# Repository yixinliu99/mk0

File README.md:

# mk0
Modularized Keyboard 0

The goal of this project is to build a full-fledged and modularized keyboard from scratch, including PCBs and a case.

# Prelude
The last time I designed a PCB was for the final project of my Bachelor degree, which was almost 4 years ago. Some refreshing on how to design PCB is definetely needed for me. I have found https://wiki.ai03.com/books/pcb-design/chapter/pcb-designer-guide pretty useful as it covers not only general PCB designing but also how keyboards work.

# Roadmap
- PCB design (keyboard + STM32F303)
- Firmware. Probably will use some code from QMK (https://github.com/qmk/qmk_firmware)
- Case design
- Fabrication

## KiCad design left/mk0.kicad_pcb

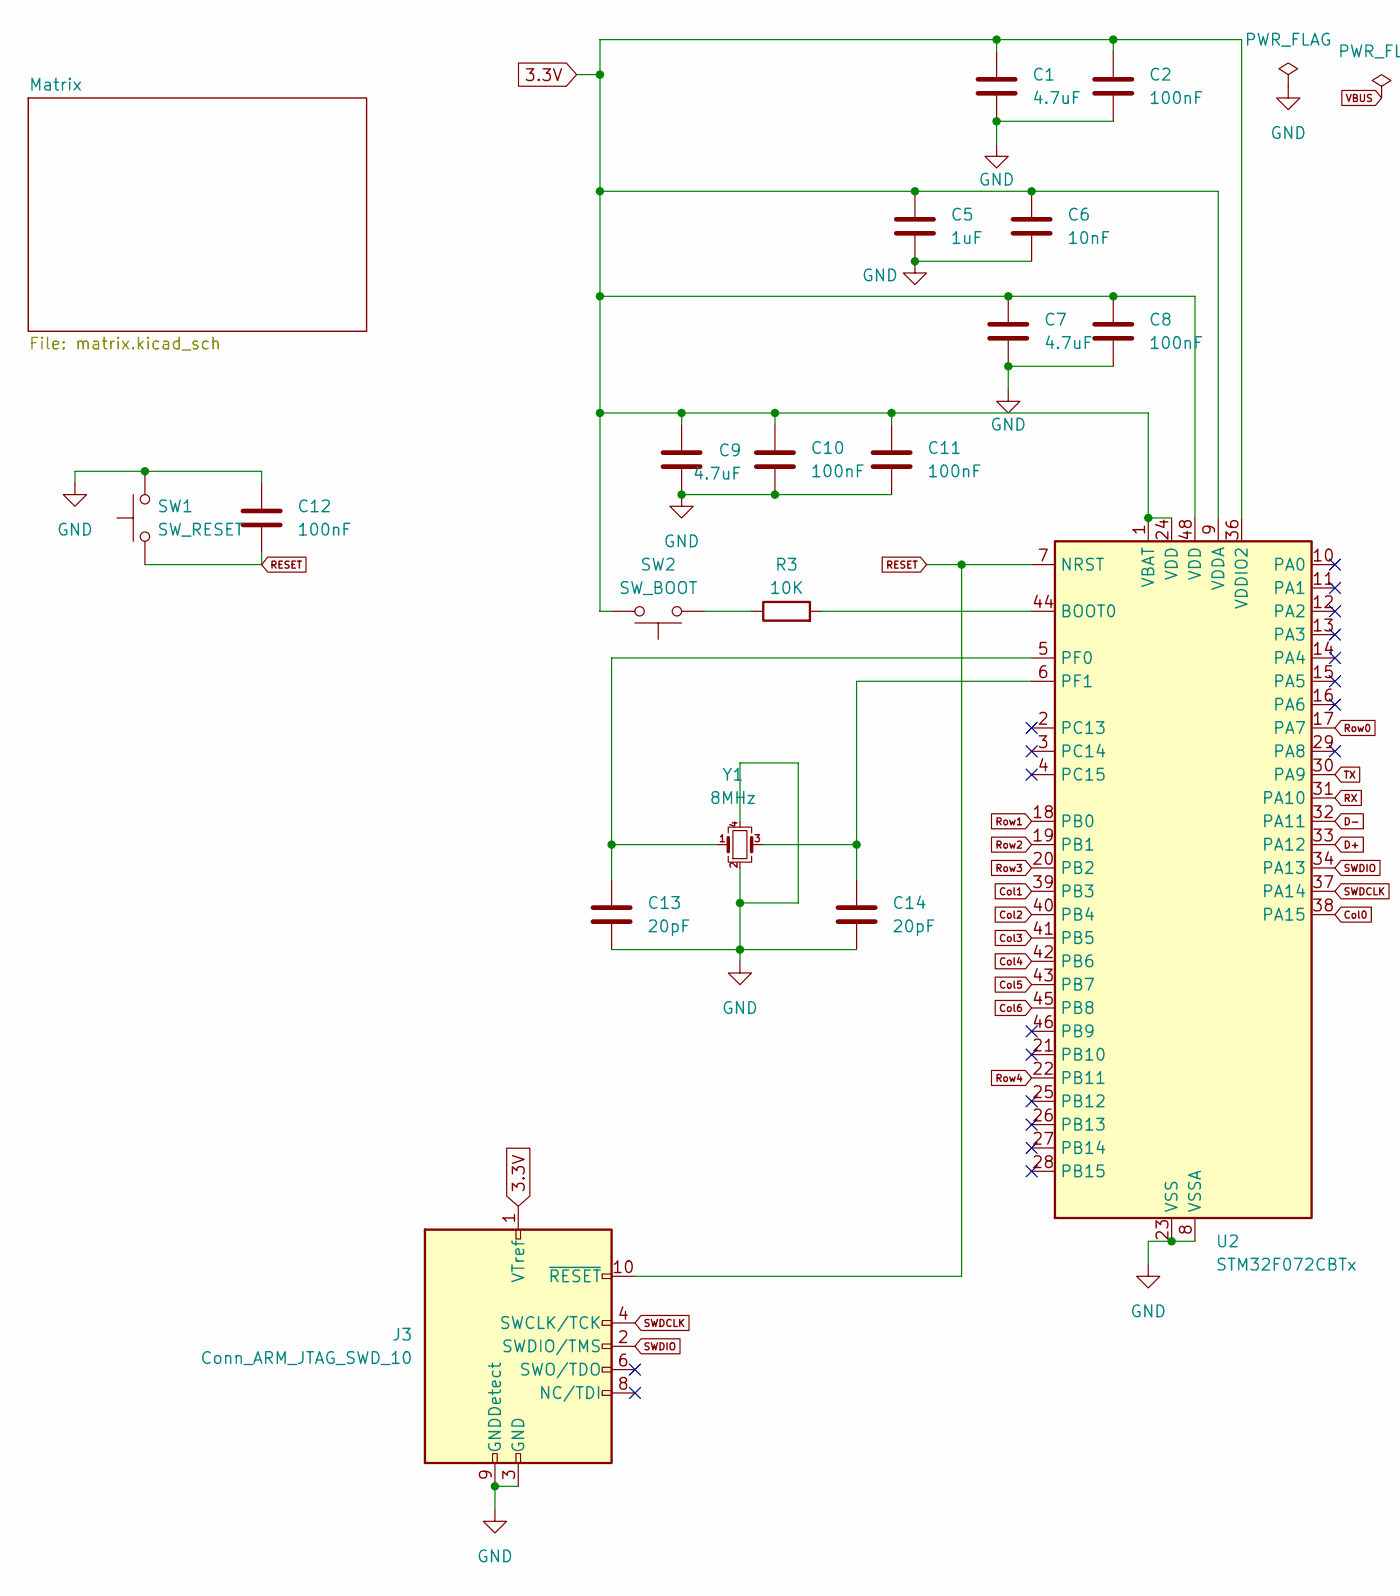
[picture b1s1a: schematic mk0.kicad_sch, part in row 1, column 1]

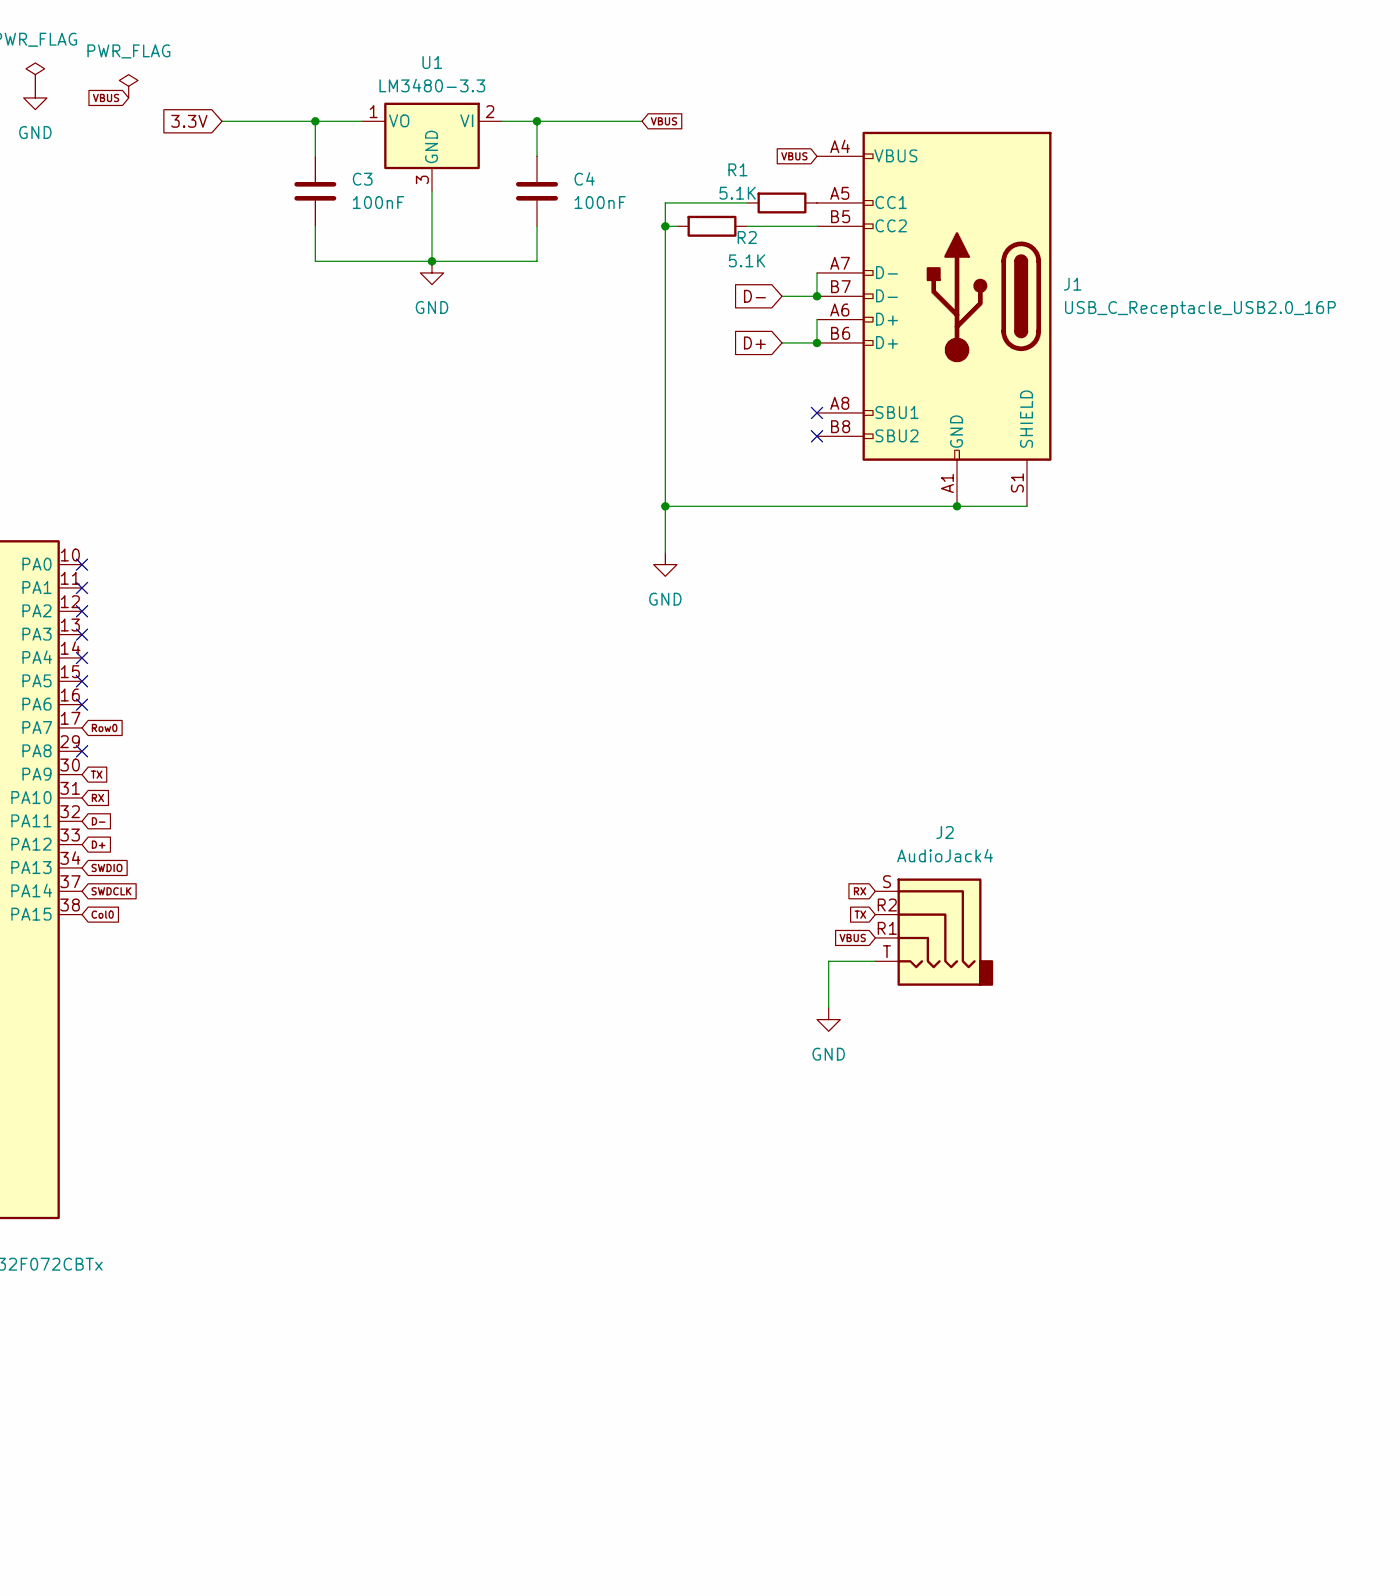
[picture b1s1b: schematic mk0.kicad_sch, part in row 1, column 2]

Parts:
C1, C7, C9: 4.7uF; C_0805_2012Metric_Pad1.18x1.45mm_HandSolder
C2, C3, C4, C8, C10, C11, C12: 100nF; C_0805_2012Metric_Pad1.18x1.45mm_HandSolder
C5: 1uF; C_0805_2012Metric_Pad1.18x1.45mm_HandSolder
C6: 10nF; C_0805_2012Metric_Pad1.18x1.45mm_HandSolder
C13, C14: 20pF; C_0805_2012Metric_Pad1.18x1.45mm_HandSolder
J1: USB_C_Receptacle_USB2.0_16P; USB_C_Receptacle_HRO_TYPE-C-31-M-12
J2: AudioJack4; Plug_3.5mm_CUI_SP-3541
J3: Conn_ARM_JTAG_SWD_10; Harwin_M20-89010xx_1x10_P2.54mm_Horizontal
R1, R2: 5.1K; R_0805_2012Metric_Pad1.20x1.40mm_HandSolder
R3: 10K; R_0805_2012Metric_Pad1.20x1.40mm_HandSolder
SW1: SW_RESET; SW_SPST_CK_RS282G05A3
SW2: SW_BOOT; SW_SPST_CK_RS282G05A3
U1: LM3480-3.3; SOT-23
U2: STM32F072CBTx; LQFP-48_7x7mm_P0.5mm
Y1: 8MHz; Crystal_SMD_3225-4Pin_3.2x2.5mm_HandSoldering

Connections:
3.3V: C1.1, C2.1, C3.1, C5.1, C6.1, C7.1, C8.1, C9.1, C10.1, C11.1, J3.1 (VTref), SW2.2, U1.1 (VO), U2.1 (VBAT), U2.9 (VDDA), U2.24 (VDD), U2.36 (VDDIO2), U2.48 (VDD)
Col0: U2.38 (PA15); also elsewhere on the board
Col1: U2.39 (PB3); also elsewhere on the board
Col2: U2.40 (PB4); also elsewhere on the board
Col3: U2.41 (PB5); also elsewhere on the board
Col4: U2.42 (PB6); also elsewhere on the board
Col5: U2.43 (PB7); also elsewhere on the board
Col6: U2.45 (PB8); also elsewhere on the board
D+: J1.A6 (D+), J1.B6 (D+), U2.33 (PA12)
D-: J1.A7 (D-), J1.B7 (D-), U2.32 (PA11)
GND: C1.2, C2.2, C3.2, C4.2, C5.2, C6.2, C7.2, C8.2, C9.2, C10.2, C11.2, C12.1, C13.2, C14.2, J1.A1 (GND), J1.A12 (GND), J1.B1 (GND), J1.B12 (GND), J1.S1 (SHIELD), J2.T, J3.3 (GND), J3.5 (GND), J3.9 (GNDDetect), R1.2, R2.2, SW1.2, U1.3 (GND), U2.8 (VSSA), U2.23 (VSS), U2.35 (VSS), U2.47 (VSS), Y1.2, Y1.4
unnamed: J1.A5 (CC1), R1.1
unnamed: J1.B5 (CC2), R2.1
unnamed: R3.1, SW2.1
unnamed: R3.2, U2.44 (BOOT0)
unnamed: C13.1, U2.5 (PF0), Y1.1
unnamed: C14.1, U2.6 (PF1), Y1.3
RESET: C12.2, J3.10 (~RESET), SW1.1, U2.7 (NRST)
RX: J2.S, U2.31 (PA10)
Row0: U2.17 (PA7); also elsewhere on the board
Row1: U2.18 (PB0); also elsewhere on the board
Row2: U2.19 (PB1); also elsewhere on the board
Row3: U2.20 (PB2); also elsewhere on the board
Row4: U2.22 (PB11); also elsewhere on the board
SWDCLK: J3.4 (SWCLK/TCK), U2.37 (PA14)
SWDIO: J3.2 (SWDIO/TMS), U2.34 (PA13)
TX: J2.R2, U2.30 (PA9)
VBUS: C4.1, J1.A4 (VBUS), J1.A9 (VBUS), J1.B4 (VBUS), J1.B9 (VBUS), J2.R1, U1.2 (VI)

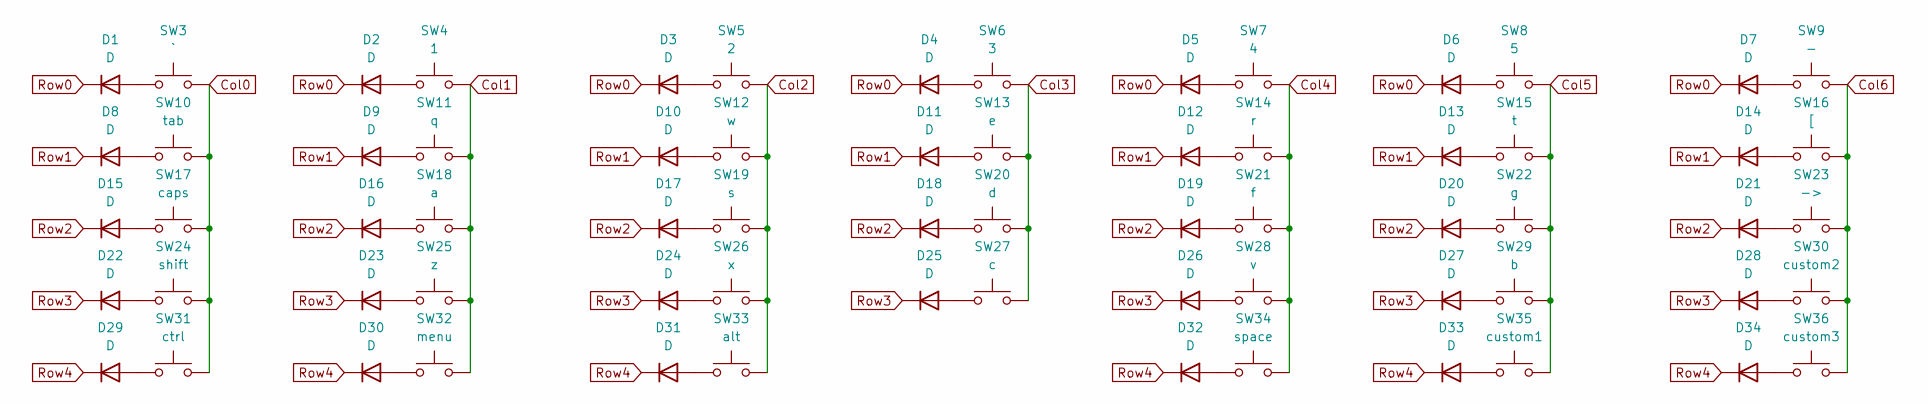
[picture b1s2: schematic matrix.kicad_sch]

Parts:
D1, D2, D3, D4, D5, D6, D7, D8, D9, D10, D11, D12, D13, D14, D15, D16, D17, D18, D19, D20, D21, D22, D23, D24, D25, D26, D27, D28, D29, D30, D31, D32, D33, D34: D; D_SOD-323_HandSoldering
SW3: `; SW_Cherry_MX_1.00u_Plate
SW4: 1; SW_Cherry_MX_1.00u_Plate
SW5: 2; SW_Cherry_MX_1.00u_Plate
SW6: 3; SW_Cherry_MX_1.00u_Plate
SW7: 4; SW_Cherry_MX_1.00u_Plate
SW8: 5; SW_Cherry_MX_1.00u_Plate
SW9: -; SW_Cherry_MX_1.00u_Plate
SW10: tab; SW_Cherry_MX_1.00u_Plate
SW11: q; SW_Cherry_MX_1.00u_Plate
SW12: w; SW_Cherry_MX_1.00u_Plate
SW13: e; SW_Cherry_MX_1.00u_Plate
SW14: r; SW_Cherry_MX_1.00u_Plate
SW15: t; SW_Cherry_MX_1.00u_Plate
SW16: [; SW_Cherry_MX_1.00u_Plate
SW17: caps; SW_Cherry_MX_1.00u_Plate
SW18: a; SW_Cherry_MX_1.00u_Plate
SW19: s; SW_Cherry_MX_1.00u_Plate
SW20: d; SW_Cherry_MX_1.00u_Plate
SW21: f; SW_Cherry_MX_1.00u_Plate
SW22: g; SW_Cherry_MX_1.00u_Plate
SW23: ->; SW_Cherry_MX_1.00u_Plate
SW24: shift; SW_Cherry_MX_1.00u_Plate
SW25: z; SW_Cherry_MX_1.00u_Plate
SW26: x; SW_Cherry_MX_1.00u_Plate
SW27: c; SW_Cherry_MX_1.00u_Plate
SW28: v; SW_Cherry_MX_1.00u_Plate
SW29: b; SW_Cherry_MX_1.00u_Plate
SW30: custom2; SW_Cherry_MX_1.00u_Plate
SW31: ctrl; SW_Cherry_MX_1.00u_Plate
SW32: menu; SW_Cherry_MX_1.00u_Plate
SW33: alt; SW_Cherry_MX_1.00u_Plate
SW34: space; SW_Cherry_MX_1.00u_Plate
SW35: custom1; SW_Cherry_MX_1.00u_Plate
SW36: custom3; SW_Cherry_MX_1.00u_Plate

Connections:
Col0: SW3.2, SW10.2, SW17.2, SW24.2, SW31.2; also elsewhere on the board
Col1: SW4.2, SW11.2, SW18.2, SW25.2, SW32.2; also elsewhere on the board
Col2: SW5.2, SW12.2, SW19.2, SW26.2, SW33.2; also elsewhere on the board
Col3: SW6.2, SW13.2, SW20.2, SW27.2; also elsewhere on the board
Col4: SW7.2, SW14.2, SW21.2, SW28.2, SW34.2; also elsewhere on the board
Col5: SW8.2, SW15.2, SW22.2, SW29.2, SW35.2; also elsewhere on the board
Col6: SW9.2, SW16.2, SW23.2, SW30.2, SW36.2; also elsewhere on the board
unnamed: D1.2 (A), SW3.1
unnamed: D2.2 (A), SW4.1
unnamed: D3.2 (A), SW5.1
unnamed: D4.2 (A), SW6.1
unnamed: D5.2 (A), SW7.1
unnamed: D6.2 (A), SW8.1
unnamed: D7.2 (A), SW9.1
unnamed: D8.2 (A), SW10.1
unnamed: D9.2 (A), SW11.1
unnamed: D10.2 (A), SW12.1
unnamed: D11.2 (A), SW13.1
unnamed: D12.2 (A), SW14.1
unnamed: D13.2 (A), SW15.1
unnamed: D14.2 (A), SW16.1
unnamed: D15.2 (A), SW17.1
unnamed: D16.2 (A), SW18.1
unnamed: D17.2 (A), SW19.1
unnamed: D18.2 (A), SW20.1
unnamed: D19.2 (A), SW21.1
unnamed: D20.2 (A), SW22.1
unnamed: D21.2 (A), SW23.1
unnamed: D22.2 (A), SW24.1
unnamed: D23.2 (A), SW25.1
unnamed: D24.2 (A), SW26.1
unnamed: D25.2 (A), SW27.1
unnamed: D26.2 (A), SW28.1
unnamed: D27.2 (A), SW29.1
unnamed: D28.2 (A), SW30.1
unnamed: D29.2 (A), SW31.1
unnamed: D30.2 (A), SW32.1
unnamed: D31.2 (A), SW33.1
unnamed: D32.2 (A), SW34.1
unnamed: D33.2 (A), SW35.1
unnamed: D34.2 (A), SW36.1
Row0: D1.1 (K), D2.1 (K), D3.1 (K), D4.1 (K), D5.1 (K), D6.1 (K), D7.1 (K); also elsewhere on the board
Row1: D8.1 (K), D9.1 (K), D10.1 (K), D11.1 (K), D12.1 (K), D13.1 (K), D14.1 (K); also elsewhere on the board
Row2: D15.1 (K), D16.1 (K), D17.1 (K), D18.1 (K), D19.1 (K), D20.1 (K), D21.1 (K); also elsewhere on the board
Row3: D22.1 (K), D23.1 (K), D24.1 (K), D25.1 (K), D26.1 (K), D27.1 (K), D28.1 (K); also elsewhere on the board
Row4: D29.1 (K), D30.1 (K), D31.1 (K), D32.1 (K), D33.1 (K), D34.1 (K); also elsewhere on the board

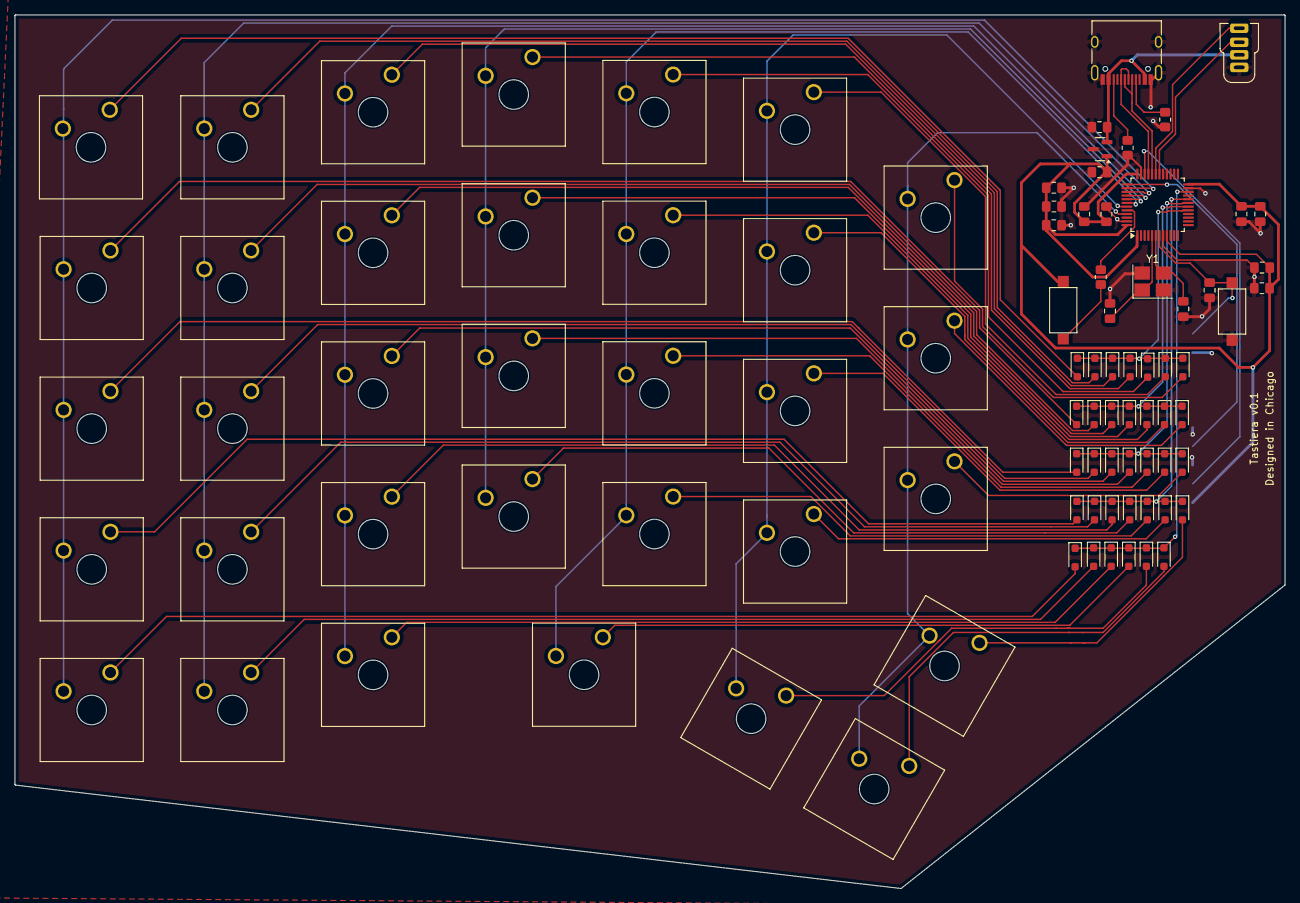
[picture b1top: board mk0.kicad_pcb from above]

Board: 2 copper layers, 172.0 x 118.3 mm, 93 parts (1 on the bottom side), 62 nets.

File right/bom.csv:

Id,Designator,Footprint,Quantity,Designation,Supplier and ref
1,"C11,C3,C4,C12,C8,C10,C2",C_0805_2012Metric_Pad1.18x1.45mm_HandSolder,7,100nF,
,,,,,
,,,,,
,,,,,
5,SW2,SW_SPST_CK_RS282G05A3,1,SW_BOOT,
,,,,,
7,"D20,D33,D3,D6,D27,D21,D28,D5,D23,D10,D18,D1,D25,D2,D19,D4,D30,D24,D11,D16,D31,D29,D13,D26,D7,D9,D12,D17,D32,D8,D22,D14,D15",D_SOD-323_HandSoldering,33,D,
,,,,,
,,,,,
,,,,,
11,U1,SOT-23,1,LM3480-3.3,
,,,,,
13,R3,R_0805_2012Metric_Pad1.20x1.40mm_HandSolder,1,10K,
,,,,,
15,"C1,C9,C7",C_0805_2012Metric_Pad1.18x1.45mm_HandSolder,3,4.7uF,
16,"C14,C13",C_0805_2012Metric_Pad1.18x1.45mm_HandSolder,2,20pF,
17,J2,Plug_3.5mm_CUI_SP-3541,1,AudioJack4,
18,C5,C_0805_2012Metric_Pad1.18x1.45mm_HandSolder,1,1uF,
,,,,,
,,,,,
21,J1,USB_C_Receptacle_HRO_TYPE-C-31-M-12,1,USB_C_Receptacle_USB2.0_16P,
22,"R2,R1",R_0805_2012Metric_Pad1.20x1.40mm_HandSolder,2,5.1K,
,,,,,
,,,,,
,,,,,
,,,,,
,,,,,
,,,,,
,,,,,
,,,,,
,,,,,
,,,,,
33,U2,LQFP-48_7x7mm_P0.5mm,1,STM32F072CBTx,
34,SW1,SW_SPST_CK_RS282G05A3,1,SW_RESET,
,,,,,
36,Y1,Crystal_SMD_2012-2Pin_2.0x1.2mm_HandSoldering,1,8MHz,
,,,,,
,,,,,
,,,,,
,,,,,
41,C6,C_0805_2012Metric_Pad1.18x1.45mm_HandSolder,1,10nF,
,,,,,
,,,,,
,,,,,
45,R4,R_0805_2012Metric_Pad1.20x1.40mm_HandSolder,1,390,
,,,,,
,,,,,
,,,,,
49,J3,Harwin_M20-89010xx_1x10_P2.54mm_Horizontal,1,Conn_ARM_JTAG_SWD_10,

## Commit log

2024-12-18 Completed left PCB, switches routing pending
2024-12-19 Finish routing for switches
2024-12-24 Complete left halve
2025-01-01 fix left halve & start right halve
2025-01-02 Finish right halve
2025-01-02 left halve plate holes & python script
2025-01-03 change cristals
